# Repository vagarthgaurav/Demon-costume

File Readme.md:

# Demon Costume

This project is the electronics part of a demon costume. The costume is a work in progress. The hardware design is completed. It will be eventually be integrated into the costume which is intended to be worn in festivals. 

It contains three custom PCBs. The wings open and close driven by linear actuators. It can also drive multiple RGB led chains. It is controlled wirelessly with a remote.

---

## demonBoard

The Main controller. ESP32-C3 Wroom drives two linear actuators for the wings and has connectors for the LED boards. It is powered by a 3S Lipo. 

---

## demonSpawn

The remote that controls the main board. Also an ESP32-C3 Wroom, talks to the demonBoard over ESP-now protocol. It is powered by 18650 Li-Ion cell with USB-C charging. Has 5V LED outputs so it can be integrated into something like a sword.

---

## demonLight

Small board with a single WS2813B RGB LED. Boards can be chained together and they are screwed onto 3D printed thorns.

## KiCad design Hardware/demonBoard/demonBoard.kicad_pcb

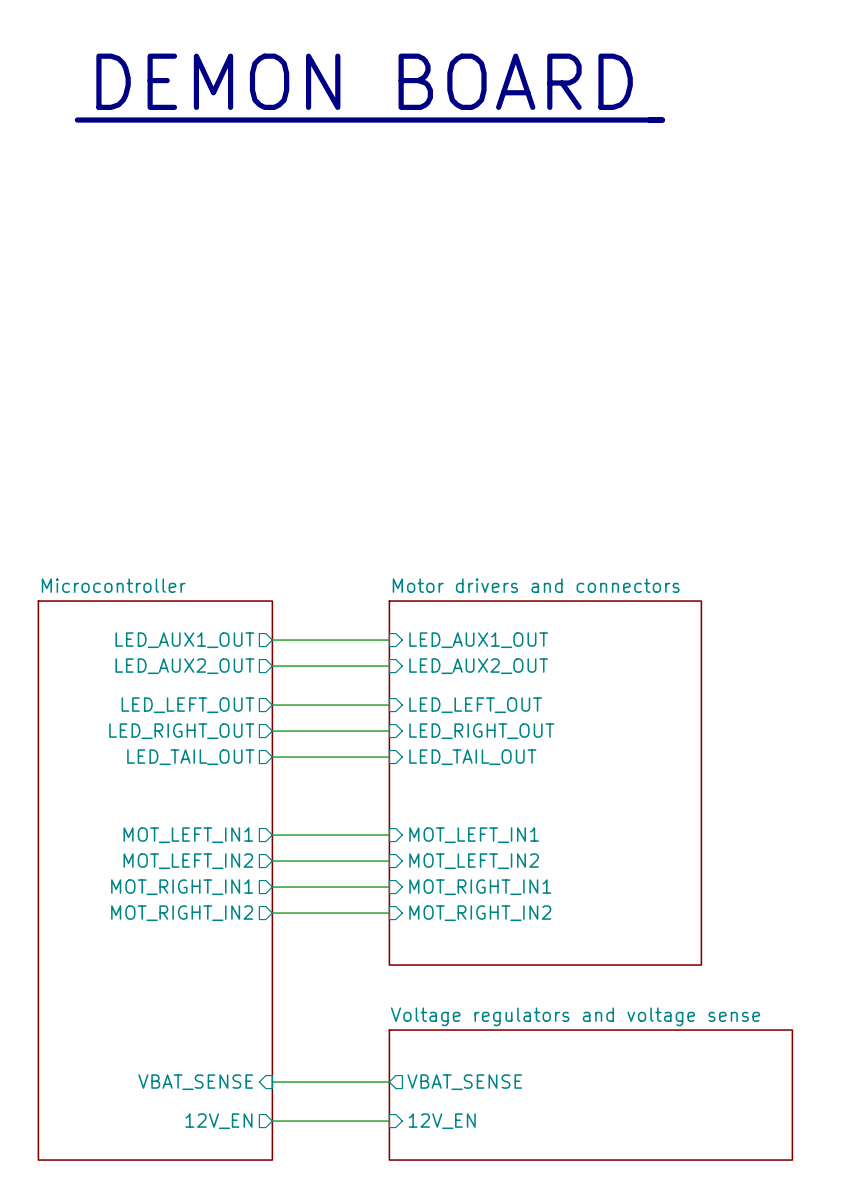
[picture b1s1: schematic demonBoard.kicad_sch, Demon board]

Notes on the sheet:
DEMON BOARD

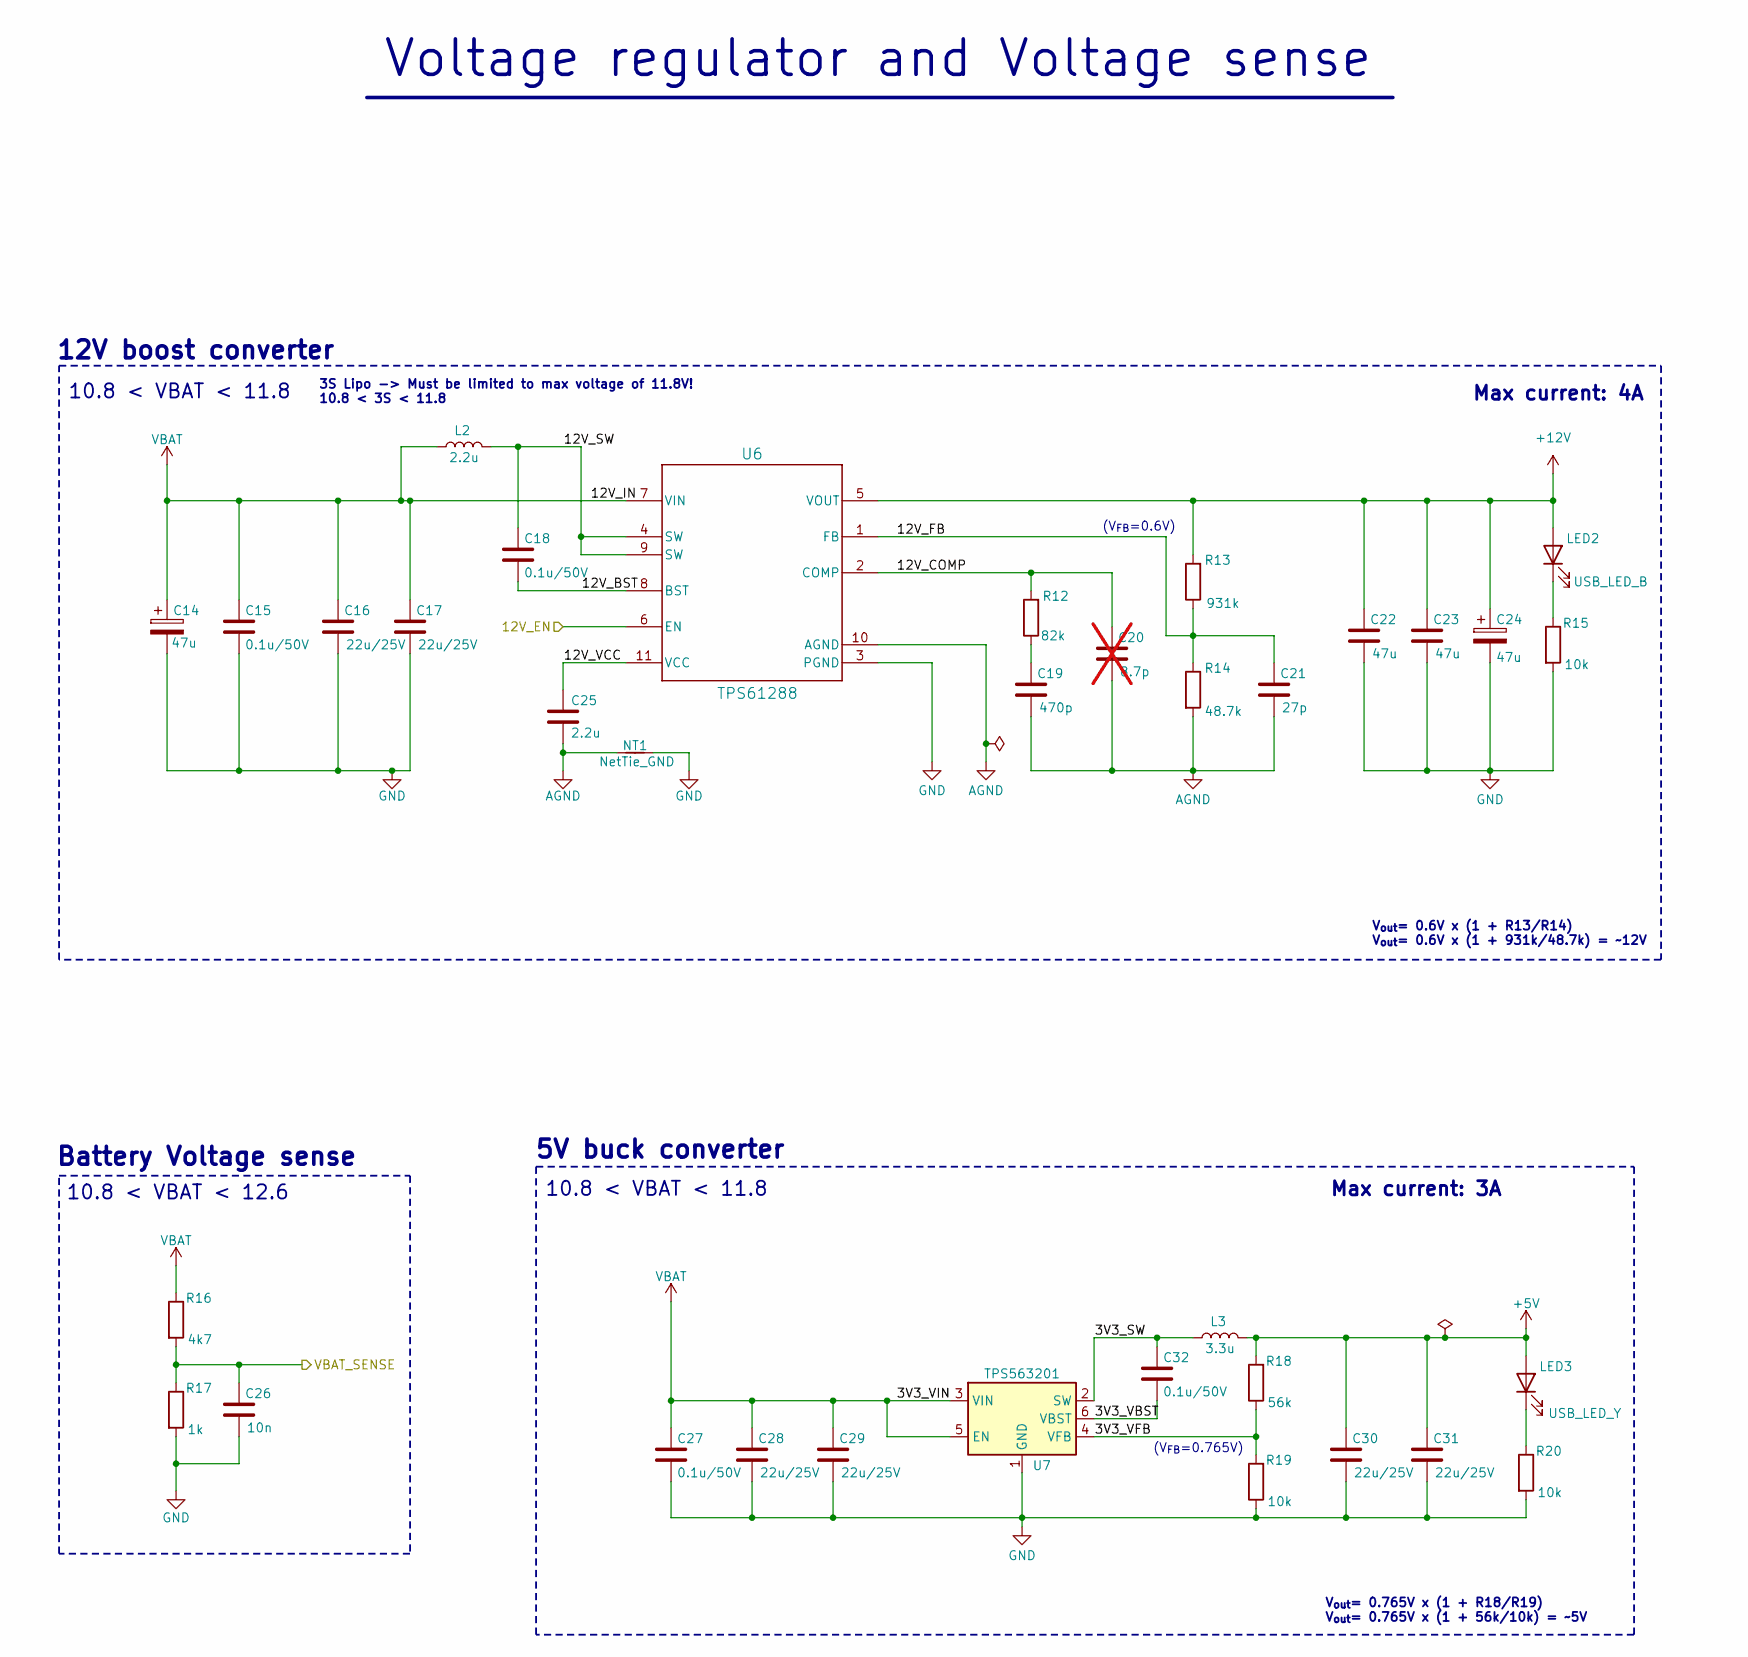
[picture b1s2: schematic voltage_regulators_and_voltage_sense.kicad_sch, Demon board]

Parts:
C14, C24: 47u; CP_Elec_6.3x7.7
C15, C18, C27, C32: 0.1u/50V; C_0603_1608Metric
C16, C17, C28, C29, C30, C31: 22u/25V; C_0805_2012Metric
C19: 470p; C_0402_1005Metric
C20: 8.7p; C_0402_1005Metric; not fitted
C21: 27p; C_0402_1005Metric
C22, C23: 47u; C_1210_3225Metric
C25: 2.2u; C_0603_1608Metric
C26: 10n; C_0402_1005Metric
L2: 2.2u; SPM6530
L3: 3.3u; L_APV_APH0530
LED2: USB_LED_B; LED_0402_1005Metric
LED3: USB_LED_Y; LED_0402_1005Metric
NT1: NetTie_GND; NetTie-2_SMD_Pad0.5mm
R12: 82k; R_0402_1005Metric
R13: 931k; R_0402_1005Metric
R14: 48.7k; R_0402_1005Metric
R15, R19, R20: 10k; R_0402_1005Metric
R16: 4k7; R_0402_1005Metric
R17: 1k; R_0402_1005Metric
R18: 56k; R_0402_1005Metric
U6: TPS61288
U7: TPS563201; SOT-23-6

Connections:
+5V: C30.1, C31.1, L3.2, LED3.2 (A), R18.2; also elsewhere on the board
+12V: C22.1, C23.1, C24.1, LED2.2 (A), R13.2, U6.5 (VOUT); also elsewhere on the board
/Microcontroller/12V_EN: U6.6 (EN); also elsewhere on the board
/Microcontroller/VBAT_SENSE: C26.1, R16.2, R17.1; also elsewhere on the board
/Voltage regulators and voltage sense/3V3_SW: C32.1, L3.1, U7.2 (SW)
/Voltage regulators and voltage sense/3V3_VBST: C32.2, U7.6 (VBST)
/Voltage regulators and voltage sense/3V3_VFB: R18.1, R19.2, U7.4 (VFB)
/Voltage regulators and voltage sense/12V_BST: C18.2, U6.8 (BST)
/Voltage regulators and voltage sense/12V_COMP: C20.1, R12.2, U6.2 (COMP)
/Voltage regulators and voltage sense/12V_FB: C21.1, R13.1, R14.1, U6.1 (FB)
/Voltage regulators and voltage sense/12V_SW: C18.1, L2.2, U6.4 (SW), U6.9 (SW)
/Voltage regulators and voltage sense/12V_VCC: C25.1, U6.11 (VCC)
AGND: C19.2, C20.2, C21.2, C25.2, NT1.1, R14.2, U6.10 (AGND)
GND: C14.2, C15.2, C16.2, C17.2, C22.2, C23.2, C24.2, C26.2, C27.2, C28.2, C29.2, C30.2, C31.2, NT1.2, R15.2, R17.2, R19.1, R20.2, U6.3 (PGND), U7.1 (GND); also elsewhere on the board
unnamed: C19.1, R12.1
unnamed: LED2.1 (K), R15.1
unnamed: LED3.1 (K), R20.1
VBAT: C14.1, C15.1, C16.1, C17.1, C27.1, C28.1, C29.1, L2.1, R16.1, U6.7 (VIN), U7.3 (VIN), U7.5 (EN); also elsewhere on the board

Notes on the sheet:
Battery Voltage sense
10.8 < VBAT < 11.8
Max current: 3A
Voltage regulator and Voltage sense
Max current: 4A
3S Lipo -> Must be limited to max voltage of 11.8V! 10.8 < 3S < 11.8
5V buck converter
(V_{FB}=0.6V)
(V_{FB}=0.765V)
V_{out}= 0.6V x (1 + R13/R14) V_{out}= 0.6V x (1 + 931k/48.7k) = ~12V
10.8 < VBAT < 12.6
V_{out}= 0.765V x (1 + R18/R19) V_{out}= 0.765V x (1 + 56k/10k) = ~5V
12V boost converter

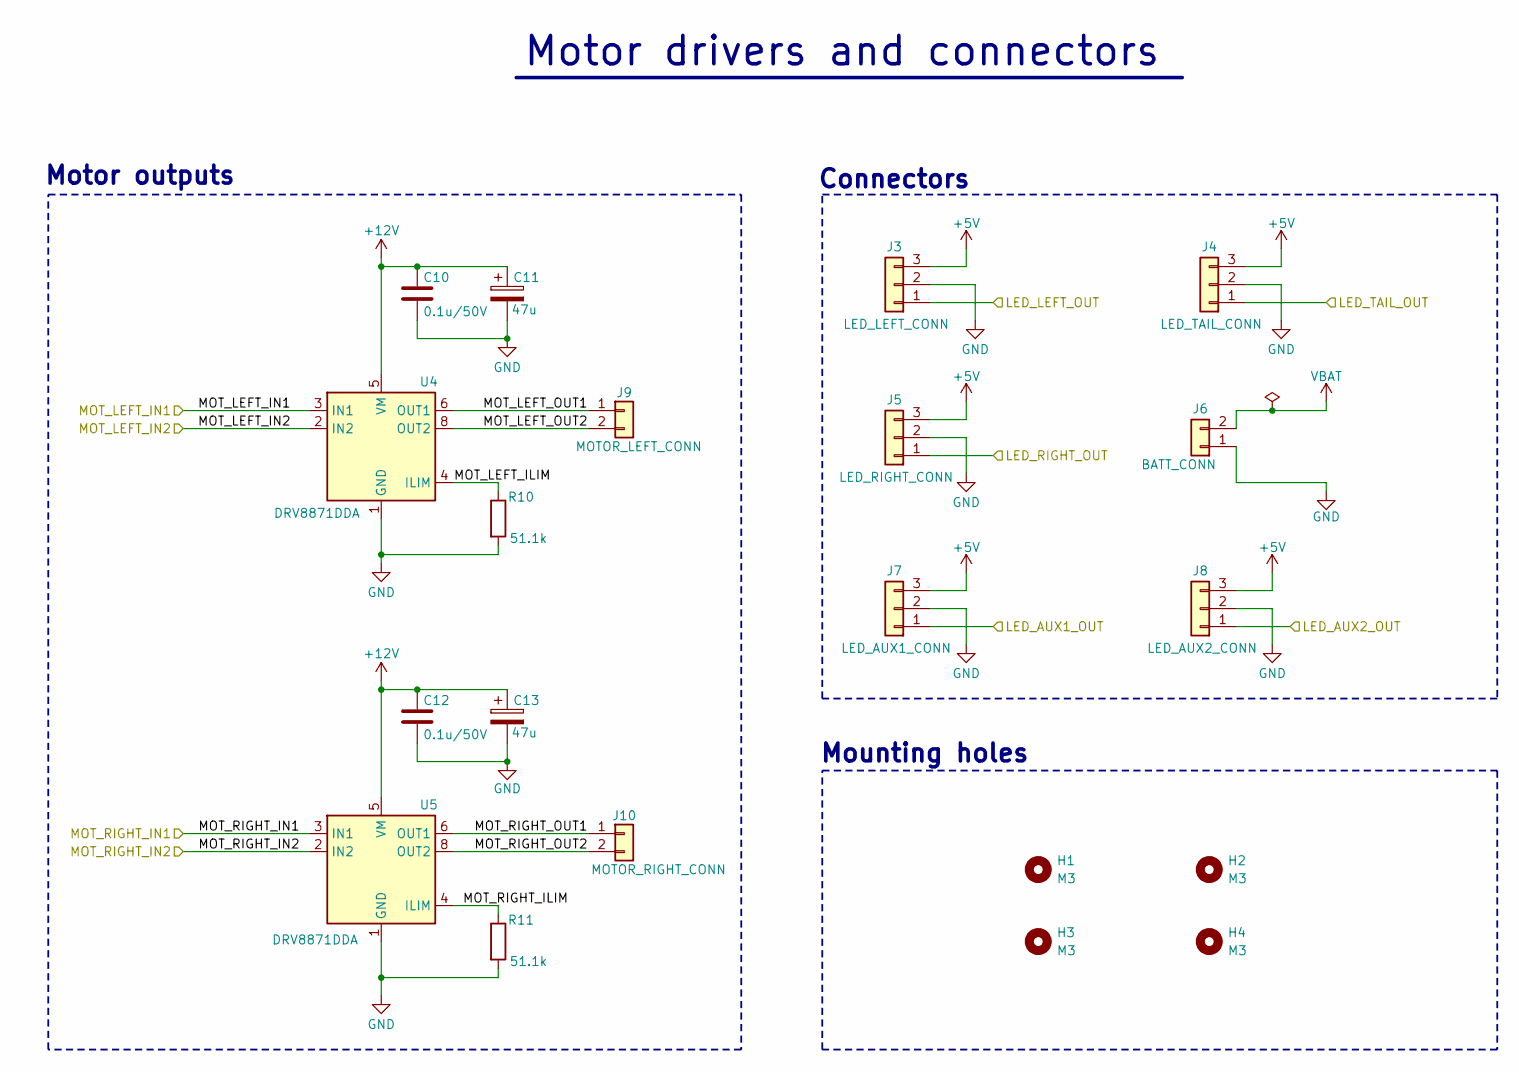
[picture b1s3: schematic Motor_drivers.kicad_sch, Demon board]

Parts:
C10, C12: 0.1u/50V; C_0603_1608Metric
C11, C13: 47u; CP_Elec_6.3x7.7
H1, H2, H3, H4: M3; MountingHole_3.2mm_M3_ISO14580_Pad_TopBottom
J3: LED_LEFT_CONN; JST_PH_S3B-PH-K_1x03_P2.00mm_Horizontal
J4: LED_TAIL_CONN; JST_PH_S3B-PH-K_1x03_P2.00mm_Horizontal
J5: LED_RIGHT_CONN; JST_PH_S3B-PH-K_1x03_P2.00mm_Horizontal
J6: BATT_CONN; AMASS_XT60PW-M_1x02_P7.20mm_Horizontal
J7: LED_AUX1_CONN; JST_PH_S3B-PH-K_1x03_P2.00mm_Horizontal
J8: LED_AUX2_CONN; JST_PH_S3B-PH-K_1x03_P2.00mm_Horizontal
J9: MOTOR_LEFT_CONN; SPTAF_1_ 2-5_0-EL
J10: MOTOR_RIGHT_CONN; SPTAF_1_ 2-5_0-EL
R10, R11: 51.1k; R_0402_1005Metric
U4, U5: DRV8871DDA; Texas_HTSOP-8-1EP_3.9x4.9mm_P1.27mm_EP2.95x4.9mm_Mask2.4x3.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

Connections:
+5V: J3.3, J4.3, J5.3, J7.3, J8.3; also elsewhere on the board
+12V: C10.1, C11.1, C12.1, C13.1, U4.5 (VM), U5.5 (VM); also elsewhere on the board
/Microcontroller/BOOT_SEL_BTN: J7.1; also elsewhere on the board
/Microcontroller/LED_AUX2_OUT: J8.1; also elsewhere on the board
/Microcontroller/LED_LEFT_OUT: J3.1; also elsewhere on the board
/Microcontroller/LED_RIGHT_OUT: J5.1; also elsewhere on the board
/Microcontroller/LED_TAIL_OUT: J4.1; also elsewhere on the board
/Motor drivers and connectors/MOT_LEFT_ILIM: R10.1, U4.4 (ILIM)
/Motor drivers and connectors/MOT_LEFT_IN1: U4.3 (IN1); also elsewhere on the board
/Motor drivers and connectors/MOT_LEFT_IN2: U4.2 (IN2); also elsewhere on the board
/Motor drivers and connectors/MOT_LEFT_OUT1: J9.1, U4.6 (OUT1)
/Motor drivers and connectors/MOT_LEFT_OUT2: J9.2, U4.8 (OUT2)
/Motor drivers and connectors/MOT_RIGHT_ILIM: R11.1, U5.4 (ILIM)
/Motor drivers and connectors/MOT_RIGHT_IN1: U5.3 (IN1); also elsewhere on the board
/Motor drivers and connectors/MOT_RIGHT_IN2: U5.2 (IN2); also elsewhere on the board
/Motor drivers and connectors/MOT_RIGHT_OUT1: J10.1, U5.6 (OUT1)
/Motor drivers and connectors/MOT_RIGHT_OUT2: J10.2, U5.8 (OUT2)
GND: C10.2, C11.2, C12.2, C13.2, J3.2, J4.2, J5.2, J6.1, J7.2, J8.2, R10.2, R11.2, U4.1 (GND), U4.7 (GND), U4.9 (GND), U5.1 (GND), U5.7 (GND), U5.9 (GND); also elsewhere on the board
VBAT: J6.2; also elsewhere on the board

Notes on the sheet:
Mounting holes
Connectors
Motor outputs
Motor drivers and connectors

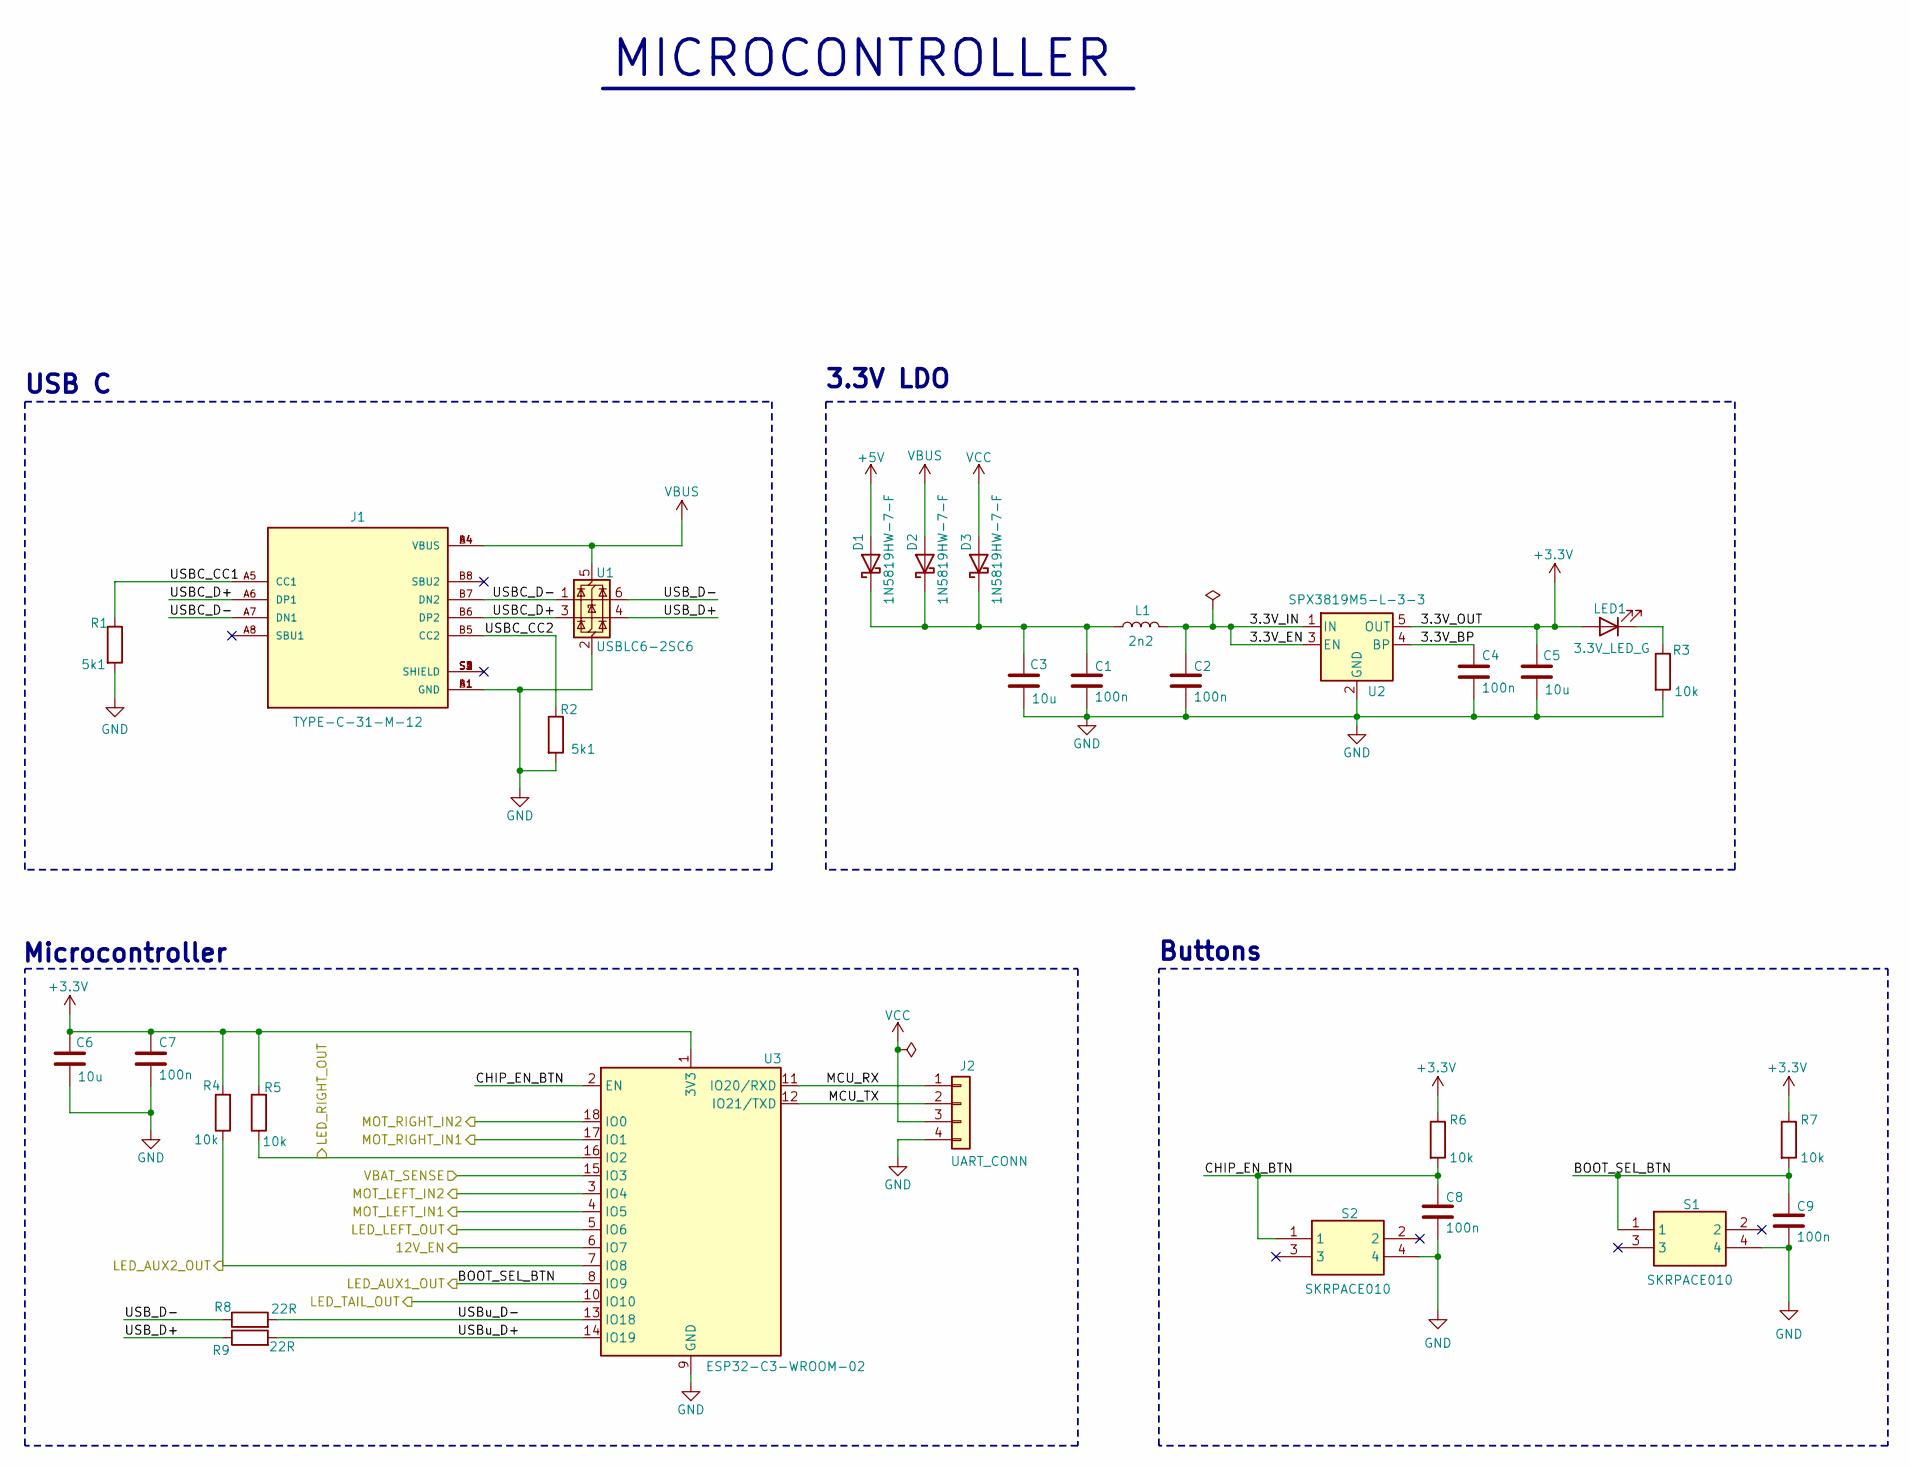
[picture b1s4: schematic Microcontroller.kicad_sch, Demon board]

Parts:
C1, C2, C4, C7, C8, C9: 100n; C_0402_1005Metric
C3, C5, C6: 10u; C_0603_1608Metric
D1, D2, D3: 1N5819HW-7-F; D_SOD-123
J1: TYPE-C-31-M-12; HRO_TYPE-C-31-M-12; PARTREV 2020.12.08
J2: UART_CONN; PinHeader_1x04_P2.54mm_Vertical
L1: 2n2; L_0402_1005Metric
LED1: 3.3V_LED_G; LED_0402_1005Metric
R1, R2: 5k1; R_0402_1005Metric
R3, R4, R5, R6, R7: 10k; R_0402_1005Metric
R8, R9: 22R; R_0402_1005Metric
S1, S2: SKRPACE010; SKRPARE010; Mouser Part Number 688-SKRPARE010
U1: USBLC6-2SC6; SOT-23-6
U2: SPX3819M5-L-3-3; SOT-23-5
U3: ESP32-C3-WROOM-02

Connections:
+3.3V: C5.1, C6.1, C7.1, LED1.2 (A), R4.2, R5.2, R6.1, R7.1, U2.5 (OUT), U3.1 (3V3)
+5V: D1.2 (A); also elsewhere on the board
/Microcontroller/3.3V_BP: C4.1, U2.4 (BP)
/Microcontroller/3.3V_EN: C2.1, L1.2, U2.1 (IN), U2.3 (EN)
/Microcontroller/12V_EN: U3.6 (IO7); also elsewhere on the board
/Microcontroller/BOOT_SEL_BTN: C9.1, R7.2, S1.1, U3.8 (IO9); also elsewhere on the board
/Microcontroller/CHIP_EN_BTN: C8.1, R6.2, S2.1, U3.2 (EN)
/Microcontroller/LED_AUX2_OUT: R4.1, U3.7 (IO8); also elsewhere on the board
/Microcontroller/LED_LEFT_OUT: U3.5 (IO6); also elsewhere on the board
/Microcontroller/LED_RIGHT_OUT: R5.1, U3.16 (IO2); also elsewhere on the board
/Microcontroller/LED_TAIL_OUT: U3.10 (IO10); also elsewhere on the board
/Microcontroller/MCU_RX: J2.1, U3.11 (IO20/RXD)
/Microcontroller/MCU_TX: J2.2, U3.12 (IO21/TXD)
/Microcontroller/USBC_CC1: J1.A5 (CC1), R1.1
/Microcontroller/USBC_CC2: J1.B5 (CC2), R2.1
/Microcontroller/USBC_D+: J1.A6 (DP1), J1.B6 (DP2), U1.3 (I/O2)
/Microcontroller/USBC_D-: J1.A7 (DN1), J1.B7 (DN2), U1.1 (I/O1)
/Microcontroller/USB_D+: R9.1, U1.4 (I/O2)
/Microcontroller/USB_D-: R8.1, U1.6 (I/O1)
/Microcontroller/USBu_D+: R9.2, U3.14 (IO19)
/Microcontroller/USBu_D-: R8.2, U3.13 (IO18)
/Microcontroller/VBAT_SENSE: U3.15 (IO3); also elsewhere on the board
/Motor drivers and connectors/MOT_LEFT_IN1: U3.4 (IO5); also elsewhere on the board
/Motor drivers and connectors/MOT_LEFT_IN2: U3.3 (IO4); also elsewhere on the board
/Motor drivers and connectors/MOT_RIGHT_IN1: U3.17 (IO1); also elsewhere on the board
/Motor drivers and connectors/MOT_RIGHT_IN2: U3.18 (IO0); also elsewhere on the board
GND: C1.2, C2.2, C3.2, C4.2, C5.2, C6.2, C7.2, C8.2, C9.2, J1.A1 (GND), J1.B1 (GND), J2.4, R1.2, R2.2, R3.2, S1.4, S2.4, U1.2 (GND), U2.2 (GND), U3.9 (GND), U3.19 (GND); also elsewhere on the board
unnamed: C1.1, C3.1, D1.1 (K), D2.1 (K), D3.1 (K), L1.1
unnamed: LED1.1 (K), R3.1
VBUS: D2.2 (A), J1.A4 (VBUS), J1.B4 (VBUS), U1.5 (VBUS)
VCC: D3.2 (A), J2.3

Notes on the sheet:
Microcontroller
MICROCONTROLLER
USB C
3.3V LDO
Buttons

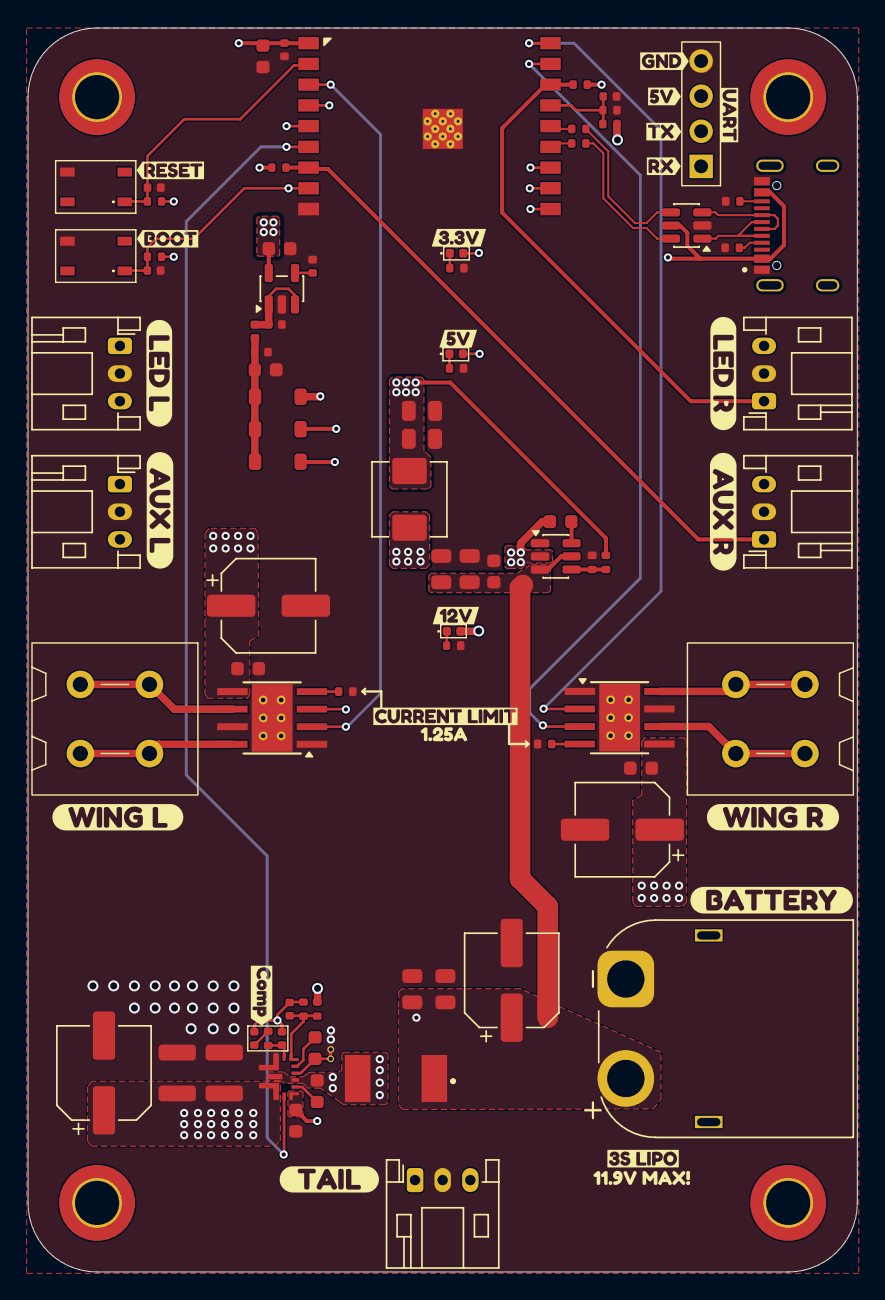
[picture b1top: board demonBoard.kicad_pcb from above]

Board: 6 copper layers, 60.0 x 90.0 mm, 108 parts (0 on the bottom side), 51 nets.

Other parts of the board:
kibuzzard-692F179E: G***; kibuzzard-692F179E
kibuzzard-6926C2DC: G***; kibuzzard-6926C2DC
kibuzzard-6926C4A5: G***; kibuzzard-6926C4A5
kibuzzard-6926C4D4: G***; kibuzzard-6926C4D4
kibuzzard-6926C5ED: G***; kibuzzard-6926C5ED
kibuzzard-6926C39D: G***; kibuzzard-6926C39D
kibuzzard-6926C40E: G***; kibuzzard-6926C40E
kibuzzard-6926C80F: G***; kibuzzard-6926C80F
kibuzzard-6926C366: G***; kibuzzard-6926C366
kibuzzard-6926C403: G***; kibuzzard-6926C403
kibuzzard-6926C417: G***; kibuzzard-6926C417
kibuzzard-6926C440: G***; kibuzzard-6926C440
kibuzzard-6926C482: G***; kibuzzard-6926C482
kibuzzard-6926C559: G***; kibuzzard-6926C559
kibuzzard-6926C567: G***; kibuzzard-6926C567
kibuzzard-6926C685: G***; kibuzzard-6926C685
kibuzzard-6926C771: G***; kibuzzard-6926C771
kibuzzard-6926C831: G***; kibuzzard-6926C831
kibuzzard-6926C843: G***; kibuzzard-6926C843
kibuzzard-6926C976: G***; kibuzzard-6926C976
kibuzzard-6926C980: G***; kibuzzard-6926C980
kibuzzard-6926CDBB: G***; kibuzzard-6926CDBB
kibuzzard-69304D0B: G***; kibuzzard-69304D0B

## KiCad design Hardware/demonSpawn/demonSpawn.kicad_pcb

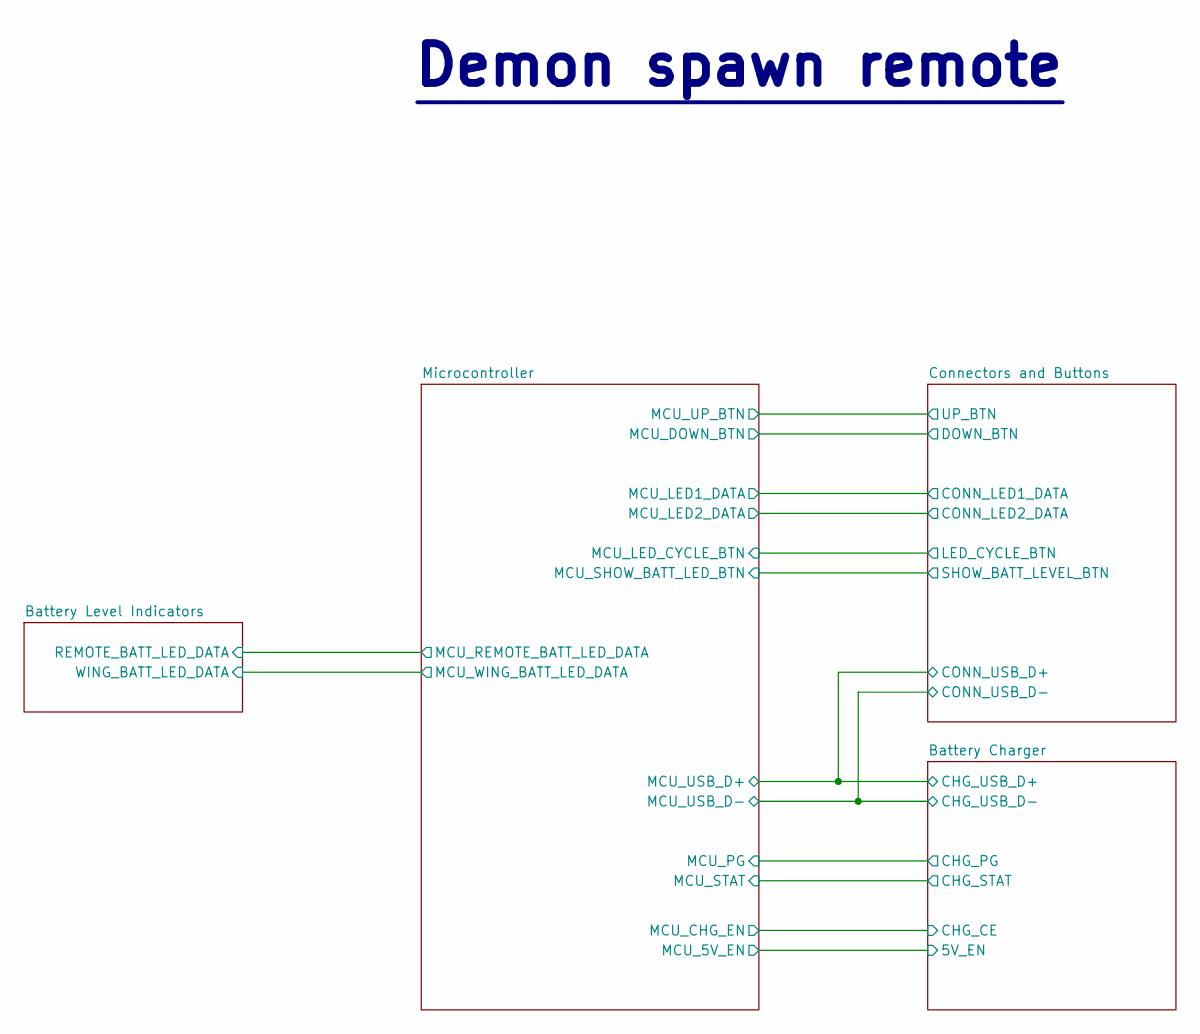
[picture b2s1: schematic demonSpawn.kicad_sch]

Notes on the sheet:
Demon spawn remote

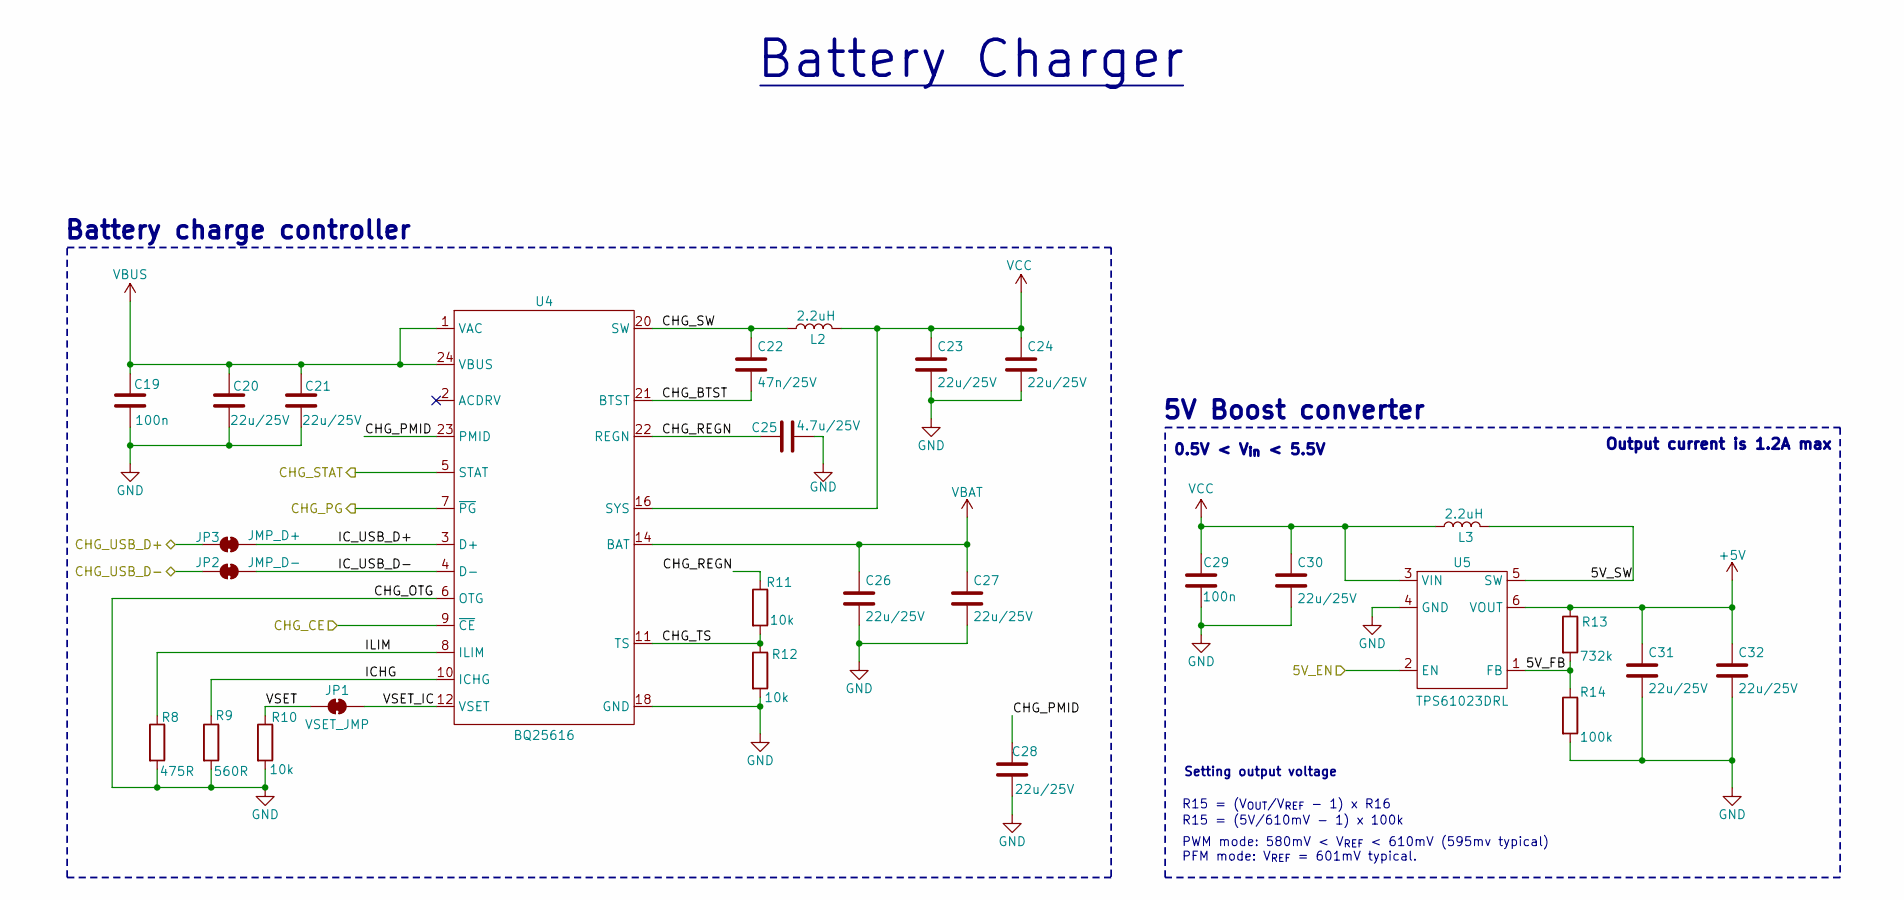
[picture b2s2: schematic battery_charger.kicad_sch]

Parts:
C19, C29: 100n; C_0402_1005Metric
C20, C21, C23, C24, C26, C27, C28, C30, C31, C32: 22u/25V; C_0805_2012Metric
C22: 47n/25V; C_0402_1005Metric
C25: 4.7u/25V; C_0603_1608Metric
JP1: VSET_JMP; SolderJumper-2_P1.3mm_Bridged_RoundedPad1.0x1.5mm
JP2: JMP_D-; SolderJumper-2_P1.3mm_Bridged_RoundedPad1.0x1.5mm
JP3: JMP_D+; SolderJumper-2_P1.3mm_Bridged_RoundedPad1.0x1.5mm
L2, L3: 2.2uH; L_Taiyo-Yuden_NR-40xx
R8: 475R; R_0402_1005Metric
R9: 560R; R_0402_1005Metric
R10, R11, R12: 10k; R_0402_1005Metric
R13: 732k; R_0402_1005Metric
R14: 100k; R_0402_1005Metric
U4: BQ25616; WQFN24_RTW_TEX-L
U5: TPS61023DRL; SOTFL50P160X60-6N

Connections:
+5V: C31.1, C32.1, R13.1, U5.6 (VOUT); also elsewhere on the board
/Battery Charger/5V_EN: U5.2 (EN); also elsewhere on the board
/Battery Charger/5V_FB: R13.2, R14.1, U5.1 (FB)
/Battery Charger/5V_SW: L3.2, U5.5 (SW)
/Battery Charger/CHG_BTST: C22.2, U4.21 (BTST)
/Battery Charger/CHG_CE: U4.9 (~CE); also elsewhere on the board
/Battery Charger/CHG_PG: U4.7 (~PG); also elsewhere on the board
/Battery Charger/CHG_PMID: C28.2, U4.23 (PMID)
/Battery Charger/CHG_REGN: C25.1, R11.1, U4.22 (REGN)
/Battery Charger/CHG_STAT: U4.5 (STAT); also elsewhere on the board
/Battery Charger/CHG_SW: C22.1, L2.1, U4.19 (SW), U4.20 (SW)
/Battery Charger/CHG_TS: R11.2, R12.1, U4.11 (TS)
/Battery Charger/CHG_USB_D+: JP3.1 (A); also elsewhere on the board
/Battery Charger/CHG_USB_D-: JP2.1 (A); also elsewhere on the board
/Battery Charger/ICHG: R9.1, U4.10 (ICHG)
/Battery Charger/IC_USB_D+: JP3.2 (B), U4.3 (D+)
/Battery Charger/IC_USB_D-: JP2.2 (B), U4.4 (D-)
/Battery Charger/ILIM: R8.1, U4.8 (ILIM)
/Battery Charger/VSET: JP1.1 (A), R10.1
/Battery Charger/VSET_IC: JP1.2 (B), U4.12 (VSET)
GND: C19.1, C20.1, C21.1, C23.2, C24.2, C25.2, C26.2, C27.2, C28.1, C29.1, C30.2, C31.2, C32.2, R8.2, R9.2, R10.2, R12.2, R14.2, U4.6 (OTG), U4.17 (GND), U4.18 (GND), U4.25 (GND), U5.4 (GND); also elsewhere on the board
VBAT: C26.1, C27.1, U4.13 (BAT), U4.14 (BAT); also elsewhere on the board
VBUS: C19.2, C20.2, C21.2, U4.1 (VAC), U4.24 (VBUS); also elsewhere on the board
VCC: C23.1, C24.1, C29.2, C30.1, L2.2, L3.1, U4.15 (SYS), U4.16 (SYS), U5.3 (VIN); also elsewhere on the board

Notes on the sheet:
0.5V < V_{in} < 5.5V
Setting output voltage
Battery Charger
R15 = (5V/610mV - 1) x 100k
R15 = (V_{OUT}/V_{REF} - 1) x R16
PWM mode: 580mV < V_{REF} < 610mV (595mv typical) PFM mode: V_{REF} = 601mV typical.
Output current is 1.2A max
Battery charge controller
5V Boost converter

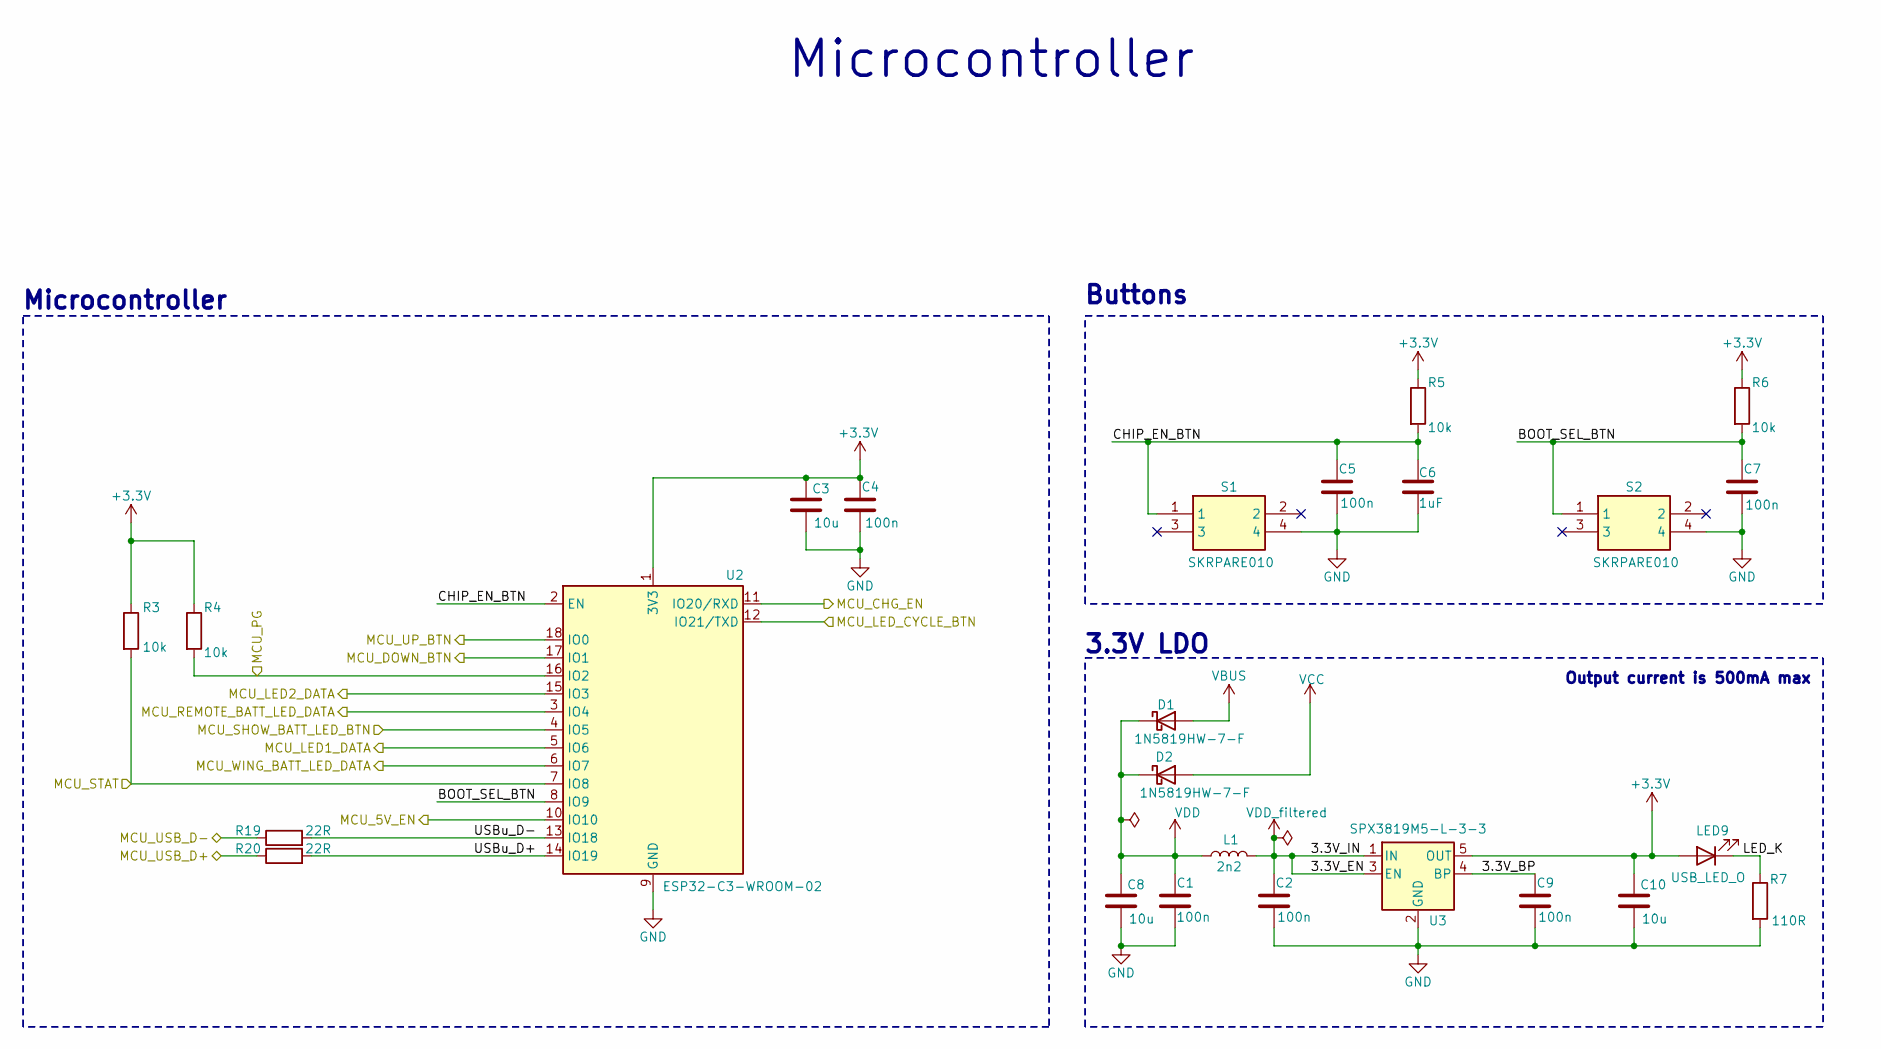
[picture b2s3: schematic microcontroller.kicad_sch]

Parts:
C1, C2, C4, C5, C7, C9: 100n; C_0402_1005Metric
C3, C8, C10: 10u; C_0603_1608Metric
C6: 1uF; C_0402_1005Metric
D1, D2: 1N5819HW-7-F; D_SOD-123
L1: 2n2; L_0402_1005Metric
LED9: USB_LED_O; LED_0402_1005Metric
R3, R4, R5, R6: 10k; R_0402_1005Metric
R7: 110R; R_0402_1005Metric
R19, R20: 22R; R_0402_1005Metric
S1, S2: SKRPARE010; Mouser Part Number 688-SKRPARE010
U2: ESP32-C3-WROOM-02
U3: SPX3819M5-L-3-3; SOT-23-5

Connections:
+3.3V: C3.1, C4.2, C10.1, LED9.2 (A), R3.1, R4.1, R5.1, R6.1, U2.1 (3V3), U3.5 (OUT); also elsewhere on the board
/Battery Charger/5V_EN: U2.10 (IO10); also elsewhere on the board
/Battery Charger/CHG_CE: U2.11 (IO20/RXD); also elsewhere on the board
/Battery Charger/CHG_PG: R4.2, U2.16 (IO2); also elsewhere on the board
/Battery Charger/CHG_STAT: R3.2, U2.7 (IO8); also elsewhere on the board
/Battery Charger/CHG_USB_D+: R20.1; also elsewhere on the board
/Battery Charger/CHG_USB_D-: R19.1; also elsewhere on the board
/Battery Level Indicators/REMOTE_BATT_LED_DATA: U2.3 (IO4); also elsewhere on the board
/Battery Level Indicators/WING_BATT_LED_DATA: U2.6 (IO7); also elsewhere on the board
/Connectors and Buttons/CONN_LED1_DATA: U2.5 (IO6); also elsewhere on the board
/Connectors and Buttons/CONN_LED2_DATA: U2.15 (IO3); also elsewhere on the board
/Connectors and Buttons/DOWN_BTN: U2.17 (IO1); also elsewhere on the board
/Connectors and Buttons/LED_CYCLE_BTN: U2.12 (IO21/TXD); also elsewhere on the board
/Connectors and Buttons/SHOW_BATT_LEVEL_BTN: U2.4 (IO5); also elsewhere on the board
/Connectors and Buttons/UP_BTN: U2.18 (IO0); also elsewhere on the board
/Microcontroller/3.3V_BP: C9.2, U3.4 (BP)
/Microcontroller/BOOT_SEL_BTN: C7.2, R6.2, S2.1, U2.8 (IO9)
/Microcontroller/CHIP_EN_BTN: C5.2, C6.1, R5.2, S1.1, U2.2 (EN)
/Microcontroller/LED_K: LED9.1 (K), R7.1
/Microcontroller/USBu_D+: R20.2, U2.14 (IO19)
/Microcontroller/USBu_D-: R19.2, U2.13 (IO18)
GND: C1.1, C2.1, C3.2, C4.1, C5.1, C6.2, C7.1, C8.2, C9.1, C10.2, R7.2, S1.4, S2.4, U2.9 (GND), U2.19 (GND), U3.2 (GND); also elsewhere on the board
VBUS: D1.2 (A); also elsewhere on the board
VCC: D2.2 (A); also elsewhere on the board
VDD: C1.2, C8.1, D1.1 (K), D2.1 (K), L1.1
VDD_filtered: C2.2, L1.2, U3.1 (IN), U3.3 (EN)

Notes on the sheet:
Output current is 500mA max
Microcontroller
Microcontroller
Buttons
3.3V LDO
